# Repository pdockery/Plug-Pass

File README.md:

# Plug-Pass

Clatskanie People's Utility District (PUD) is a public, not-for-profit electric utility, governed by a locally-elected Board of Directors serving the Oregon communities and surrounding areas of Rainier, Westport, and Clatskanie.  The vast majority of our customers commute for work, and Clatskanie PUD designed its electric vehicle to minimize cost and maximize value for its commuting customers.  

Plug-Pass is a subscription-based, electric-vehicle public charging program developed to provide commuters easy access to low-cost charging service at their workplaces.  The first deployment of the Plug-Pass program was at a location where access to the parking spots was easily monitored, and the initial offering only used timers to control electricity.  In considering ways to expand the program to locations that aren't easily monitored, staff is developing low-cost control mechanisms to enable subscribers to initiate charging while preventing unauthorized parties from easily accessing the service.

This program is designed to be open-source in the hope that by sharing the program design broadly we may be able to expand the number of utilities employing similar techniques, and thereby lower the implementation costs for offering the program to more locations in our service territory.

Included in this repository is open-source information that has been used in our pilot program:
* Form of Electric Vehicle Public Charging Rate Design<br>
* Summary of Clatskanie PUD's Electric Vehicle Public Charging Program Design<br>
* Worksheet for calculating public charging rates (pending)<br>
* Form of Plug-Pass subscription agreement (pending)

Under development in this repository are open-source projects to be deployed and tested
* Software for arduino nano based plug-pass outlet control platform
* Control board design and configuration 
* Component list for Plug-Pass outlet

<b>For more information about Clatskanie PUD's EV charging program visit:<b>
https://clatskaniepud.com/ev

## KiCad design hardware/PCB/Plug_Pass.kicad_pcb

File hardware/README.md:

# Hardware

Contains the design files for the components for the switch including 
* KiCAD files for PCB
* FreeCAD files for 3D printable housing
* Bill of materials to assemble the switch

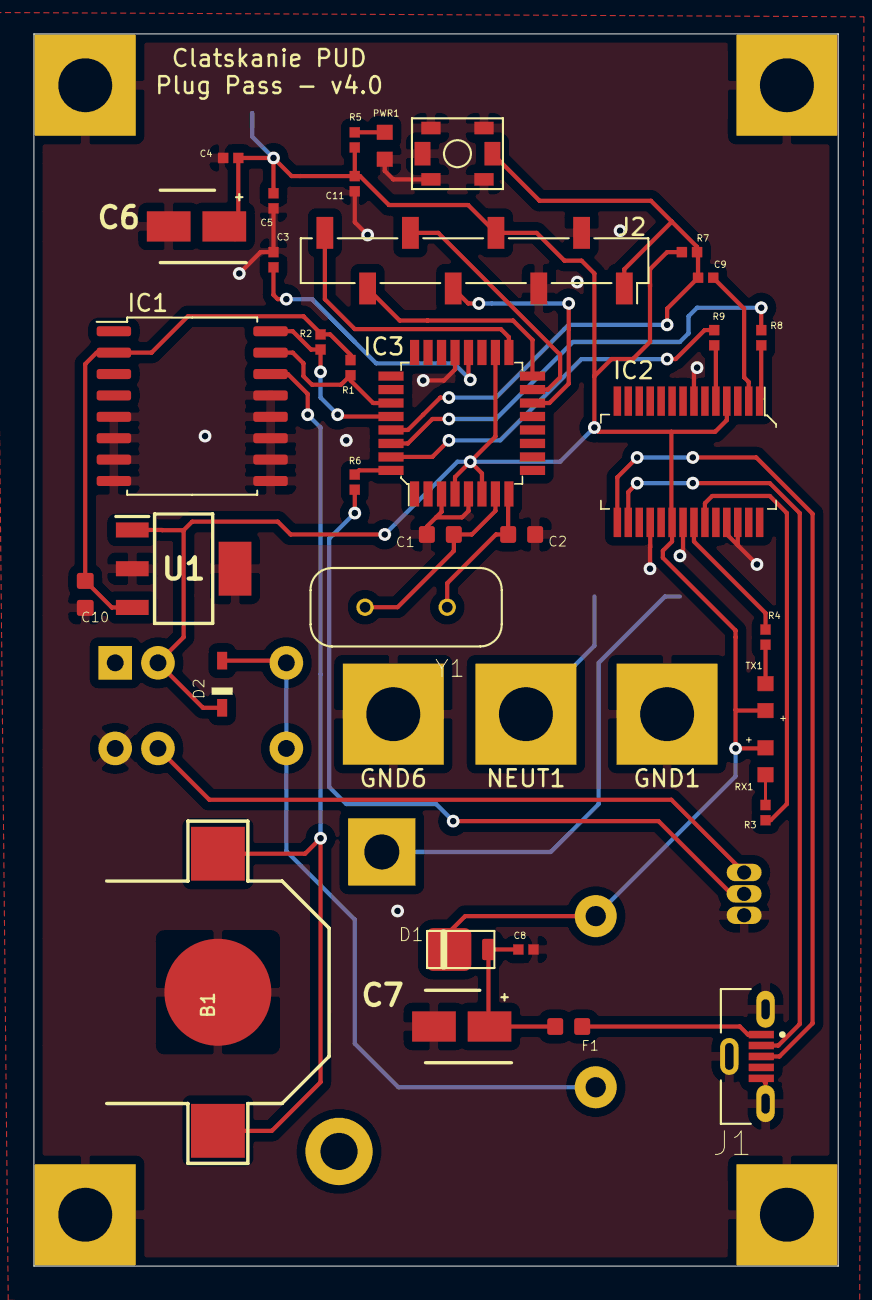
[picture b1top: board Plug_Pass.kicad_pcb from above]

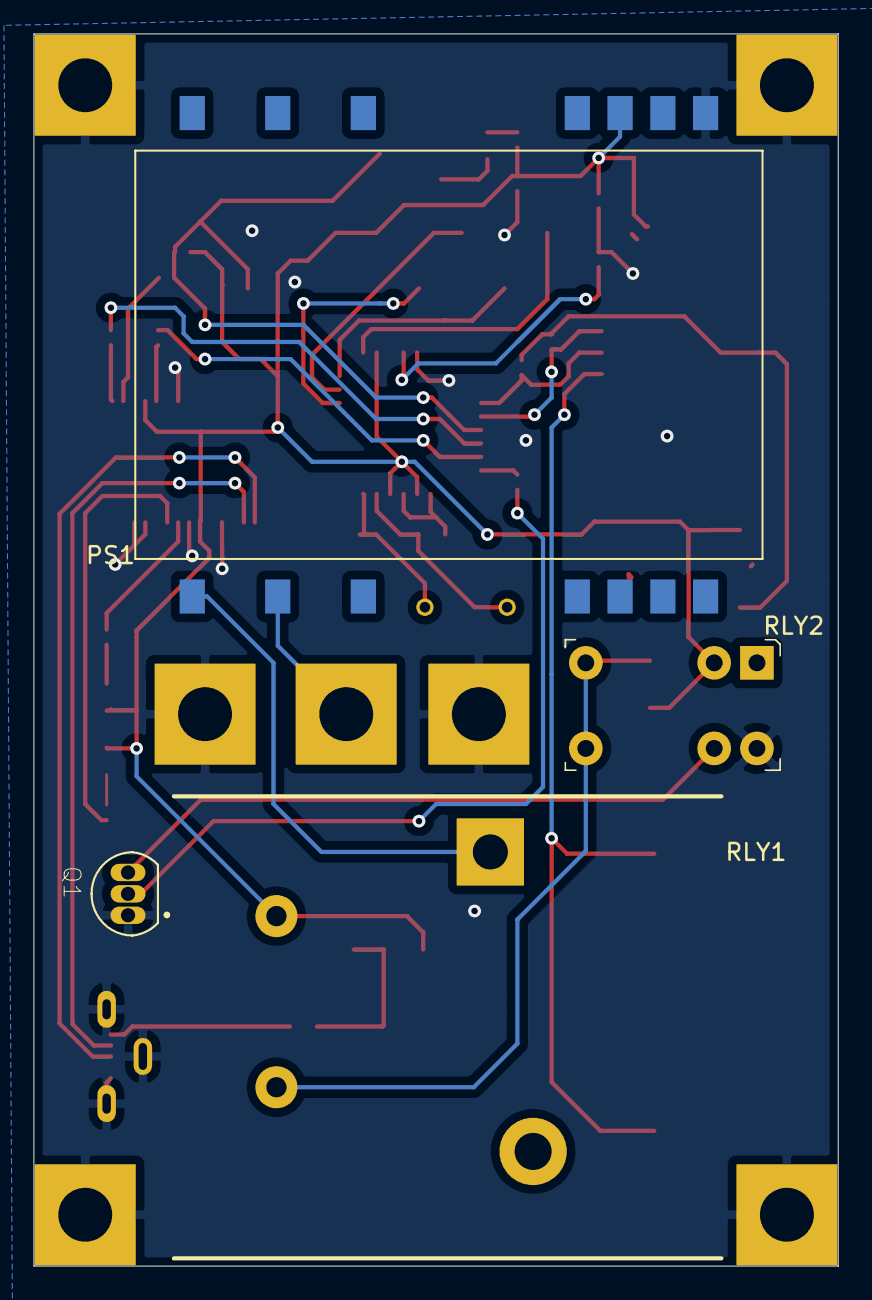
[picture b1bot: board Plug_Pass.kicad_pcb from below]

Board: 2 copper layers, 47.8 x 73.2 mm, 46 parts (4 on the bottom side), 34 nets.

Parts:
B1: CR1220
C1, C2: 22pF; 0603-1608X90N
C3, C8, C9: 100nF; 0402-1005X55N
C4, C5: 1µF; 0402-1005X55N
C6, C7: 4.7uF; CAPAE430X550N
C10: 1µF; 0603-1608X90N
C11: 1uF; 0402-1005X55N
D1: 0025_SS1P3L-M3_84A; DO220AAL
D2: 1N4148WS; SODFL2512X100N
F1: MFFSMF050; 0603-1608X90N
GND1, GND2, GND3, GND4, GND5, GND6: GND; Ground_Pad
IC1: DS3231M; SOIC-16W_7.5x10.3mm_P1.27mm
IC2: FT232RL; SSOP-28_W5.30mm
IC3: ATMEGA328P-AUR; TQFP-32_7x7mm
J1: USB_B_Micro; MOLEX_1051330001
J2: Conn_01x08; PinSocket_1x08_P2.54mm_Vertical_SMD_Pin1Right
NEUT1: NEUT; Ground_Pad
PS1: IRM-03-5; Converter_ACDC_MeanWell_IRM-03-xx_SMD
PWR1: Green; LEDC1608X80N-AK
Q1: 2N3904; TO92127P495H495-3
R1, R2: 10k; 0402-1005X55N
R3, R4, R5: 330; 0402-1005X55N
R6: 4.7k; 0402-1005X55N
R7, R8, R9: 1k; 0402-1005X55N
RLY1: T95S5D22-5; RLY-T9AS1D22-5
RLY2: G5V-1-DC5; Relay_THT_G5V-1
RX1: Red; LEDC1608X80N-AK
SW1: RESET; C&K_PTS820_NO_HOLES
TX1: Green; LEDC1608X80N-AK
U1: TC1108-3.3VDBTR; SOT230P700X180-4N
Y1: ECS-51-20-4; XTAL_ECS-51-20-4

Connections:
+3V3: C10.1, IC1.2, R1.2, R2.2, U1.3
+5V: C4.1, C5.1, C6.1, C11.1, D1.P$1, D2.C, IC2.4, IC2.20, IC3.4, IC3.6, IC3.18, J2.4, PS1.16, R5.1, R7.2, RLY1.5, RLY2.2, RX1.A, TX1.A, U1.1
/BAT+: B1.+$1, IC1.14
/D+: IC2.15, J1.3
/D-: IC2.16, J1.2
/NEUT: NEUT1.1, PS1.3
/RX_RED: IC2.23, R3.1
/TX_GREEN: IC2.22, R4.1
AC-L: PS1.1, RLY1.1
GNDREF: B1.-, C1.1, C2.1, C3.2, C4.2, C5.2, C6.2, C7.2, C8.2, C10.2, C11.2, GND1.1, GND2.1, GND3.1, GND4.1, GND5.1, GND6.1, IC1.5, IC1.6, IC1.7, IC1.8, IC1.9, IC1.10, IC1.11, IC1.12, IC1.13, IC2.7, IC2.18, IC2.21, IC2.25, IC2.26, IC3.3, IC3.5, IC3.21, J1.5, J1.S, J2.2, J2.3, PS1.14, PWR1.C, Q1.1, RLY2.10, SW1.1, SW1.3, SW1.4, SW1.5, SW1.6, U1.2, U1.4
MISO: IC3.16, J2.7
MOSI: IC3.15, J2.6
unnamed: C1.2, IC3.7, Y1.2
unnamed: C2.2, IC3.8, Y1.1
unnamed: C3.1, IC3.20
unnamed: C7.1, C8.1, D1.P$2, F1.2
unnamed: C9.2, IC2.2
unnamed: D2.A, RLY1.2, RLY2.5, RLY2.6
unnamed: F1.1, J1.1
unnamed: IC3.30, R8.1
unnamed: IC3.31, R9.1
unnamed: PWR1.A, R5.2
unnamed: Q1.2, R6.1
unnamed: Q1.3, RLY2.9
unnamed: R3.2, RX1.C
unnamed: R4.2, TX1.C
RESET: C9.1, IC3.29, J2.1, R7.1, SW1.2
RLY: IC3.32, R6.2
RX: IC2.1, R8.2
SCK: IC3.17, J2.8
SCL: IC1.16, IC3.28, R2.1
SDA: IC1.15, IC3.27, R1.1
SS: IC3.14, J2.5
TX: IC2.5, R9.2

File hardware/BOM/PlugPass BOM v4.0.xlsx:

Item # | Quantity | Reference | Value | Footprint | Description | MPN | Manufacturer | Type | Link
1.0 | 2.0 | C1, C2 | 22pF | 0603-1608X90N | Multilayer Ceramic Capacitors MLCC - SMD/SMT 22pF 50V NPO 5% | CC0603JRNPO9BN220 | Yageo | SMD | https://www.mouser.com/ProductDetail/Yageo/CC0603JRNPO9BN220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
2.0 | 3.0 | C3, C8, C9 | 100nF | 0402-1005X55N | Multilayer Ceramic Capacitors MLCC - SMD/SMT .1UF 50V 5% 0402 | GRM155R61H104JE14D | Murata Electronics | SMD
3.0 | 2.0 | C4, C5 | 1µF | 0402-1005X55N | Multilayer Ceramic Capacitors MLCC - SMD/SMT 0402 25VDC 1uF 10% | GRM155R61E105KA12D | Murata Electronics | SMD
4.0 | 2.0 | C6, C7 | 4.7µF | CAPAE430X550N | Aluminum Electrolytic Capacitors - SMD WCAP-ASNP 4.7uF 16V 20% SMD/SMT | 865250340002 | Wurth Elektronik | SMD
7.0 | 2.0 | C10, C11 | 1uF | 0402-1005X55N | Multilayer Ceramic Capacitors MLCC - SMD/SMT 0402 25VDC 1uF 10% | GRM155R61E105KA12D | Murata Electronics | SMD
8.0 | 2.0 | R1, R2 | 10k | 0402-1005X55N | Thick Film Resistors - SMD 10K OHM 1% | RC0402FR-0710KL | Yageo | SMD
9.0 | 3.0 | R3, R4, R5 | 330.0 | 0402-1005X55N | Thick Film Resistors - SMD 330 OHM 1% | RC0402FR-07330RL | Yageo | SMD
10.0 | 1.0 | R6 | 4.7k | 0402-1005X55N | Thick Film Resistors - SMD 4.7 kOhms 62.5 mW 0402 5% | RC0402JR-7D4K7L | Yageo | SMD | https://www.mouser.com/ProductDetail/Yageo/RC0402JR-7D4K7L?q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
11.0 | 3.0 | R7, R8, R9 | 1k | 0402-1005X55N | Thick Film Resistors - SMD 1 kOhms 62.5 mW 0402 5% | RC0402JR-071KL | Yageo | SMD
12.0 | 1.0 | IC1 | DS3231M | Package_SO:SOIC-16W_7.5x10.3mm_P1.27mm | Real Time Clock +/-5ppm, I C Real-Time Clock | DS3231M+ | Maxim Integrated | SMD
13.0 | 1.0 | IC2 | FT232RL | digikey-footprints:SSOP-28_W5.30mm | IC USB FS SERIAL UART 28-SSOP |  | FTDI, Future Technology Devices International Ltd | SMD
14.0 | 1.0 | IC3 | ATMEGA328P-AUR | digikey-footprints:TQFP-32_7x7mm | IC MCU 8BIT 32KB FLASH 32TQFP | ATMEGA328P-AUR | Microchip Technology | SMD
15.0 | 1.0 | SW1 | RESET | C&K_PTS820_NO_HOLES | Tactile Switches Microminiature SMT Top Actuated | PTS820J25KSMTRLFS | C&K | SMD
16.0 | 1.0 | RX1 | Red | LEDC1608X80N-AK | Standard LEDs - SMD Red Diffused 639nm 17mcd | HSMH-C190 | Broadcom | SMD
17.0 | 1.0 | TX1 | Green | LEDC1608X80N-AK | Standard LEDs - SMD Green Diffused 572nm 5mcd | HSMG-C190 | Broadcom | SMD
18.0 | 1.0 | PWR1 | Green | LEDC1608X80N-AK | Standard LEDs - SMD Green Diffused 572nm 5mcd | HSMG-C190 | Broadcom | SMD
19.0 | 1.0 | D1 | 0025_SS1P3L-M3_84A | DO220AAL | Schottky Diodes & Rectifiers 30volt 1.0amp | SS1P3L-M3/84A | Vishay Semiconductors | SMD
20.0 | 1.0 | D2 | NA | SODFL2512X100N | DIODE GEN PURP 75V 150MA SOD323F | 1N4148WS | ON Semiconductor | SMD | https://www.digikey.com/en/products/detail/on-semiconductor/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
21.0 | 1.0 | RLY1 | T9AS1D22-5 | RLY-T9AS1D22-5 | RELAY GEN PURPOSE SPST 30A 5V | T9AS1D22-5 | TE Connectivity Potter & Brumfield Relays | through-hole
22.0 | 1.0 | RLY2 | G5V-1-DC5 | Relay_THT_G5V-1 | RELAY GEN PURPOSE SPDT 1A 5VDC | G5V-1-DC5 | Omron Electronics Inc-EMC Div | through-hole
23.0 | 1.0 | B1 | CR1220 | CR1220 | CR1220 COIN CELL SM RETAINER | 2894 | Keystone Electronics | SMD
24.0 | 1.0 | Y2 | 16Mhz | HU-49USX | 16Mhz Crystal | ECS-160-18-4X-CKM | ECS | through-hole
25.0 | 1.0 | J1 | USB_B_Micro | MOLEX_1051330001 | USB Connectors MICRO USB B RECPT VERTICAL | 1051330001 | Molex | SMD & through-hole
26.0 | 1.0 | J2 | 1x8 | PinSocket_1x08_P2.54mm_Vertical_SMD_Pin1Right | CONN HDR 8POS 0.1 TIN SMD | NPTC081KFXC-RC | NA | SMD | https://www.digikey.com/en/products/detail/sullins-connector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
27.0 | 1.0 | Q1 | NA | TO-92-3 | BJT | 2n3904 | OnSemi | through-hole | https://www.mouser.com/Semiconductors/Discrete-Semiconductor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
28.0 | 1.0 | F1 | MFFSMF050 | 0603-1608X90N | Resettable Fuses - PPTC 6volts 40amps | MF-FSMF050X-2 | Bourns | SMD
29.0 | 1.0 | U1 | 3.3v | SOT-223-3 | 3.3v Regulator | TC1108-3.3VDBTR | Microchip | SMD | https://www.mouser.com/ProductDetail/579-TC1108-3.3VDBTR
30.0 | 1.0 | PS1 | IRM-03-5 | Converter_ACDC:Converter_ACDC_MeanWell_IRM-03-xx_SMD | AC/DC CONVERTER 5V 3W | IRM-03-5S | MEAN WELL USA Inc. | SMD

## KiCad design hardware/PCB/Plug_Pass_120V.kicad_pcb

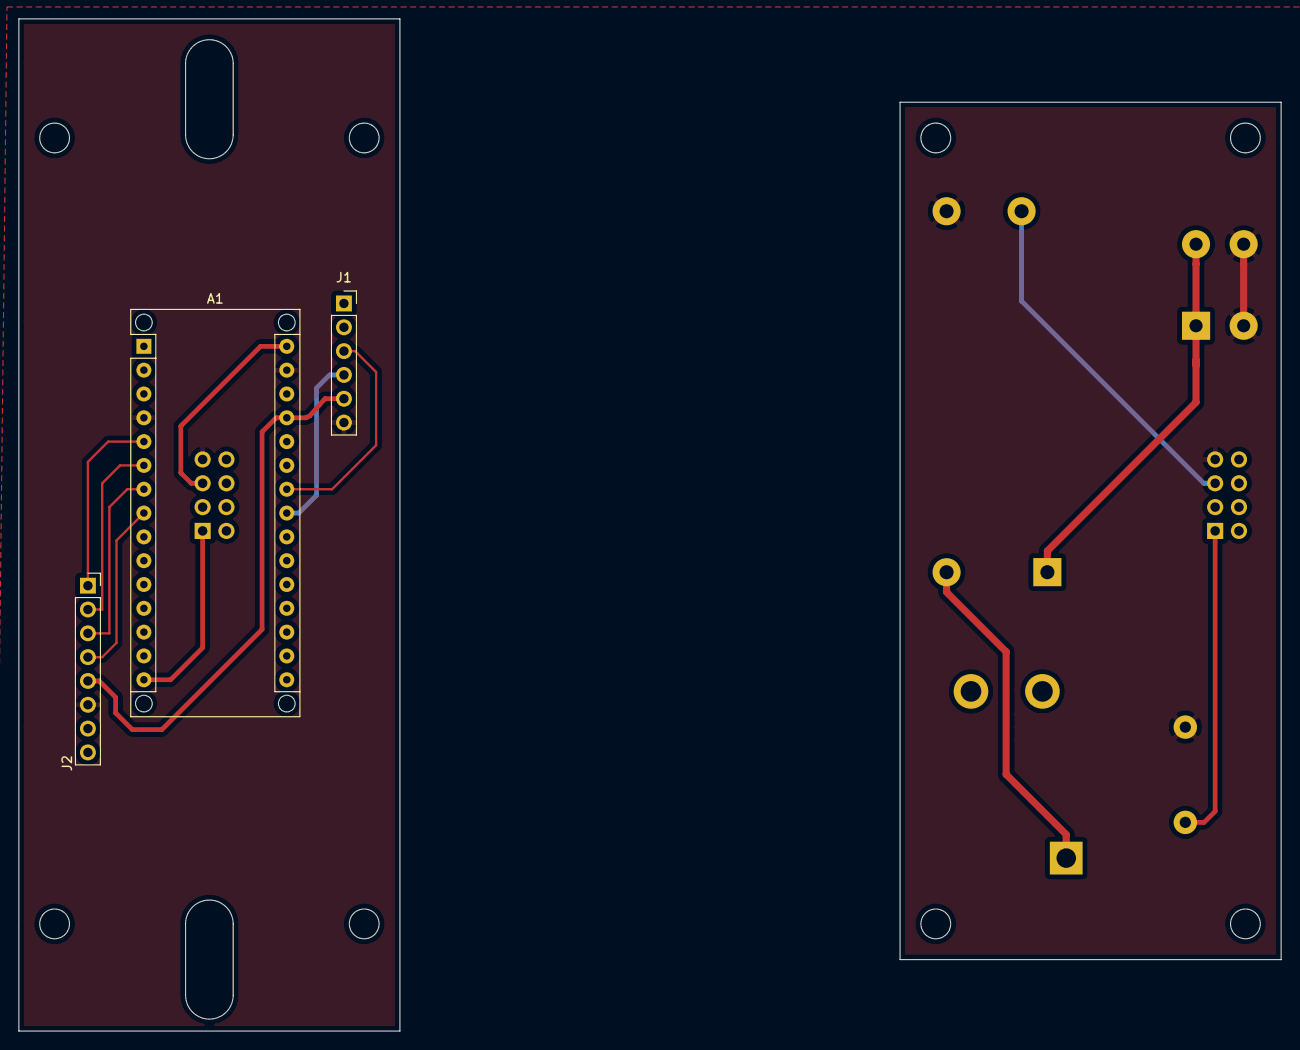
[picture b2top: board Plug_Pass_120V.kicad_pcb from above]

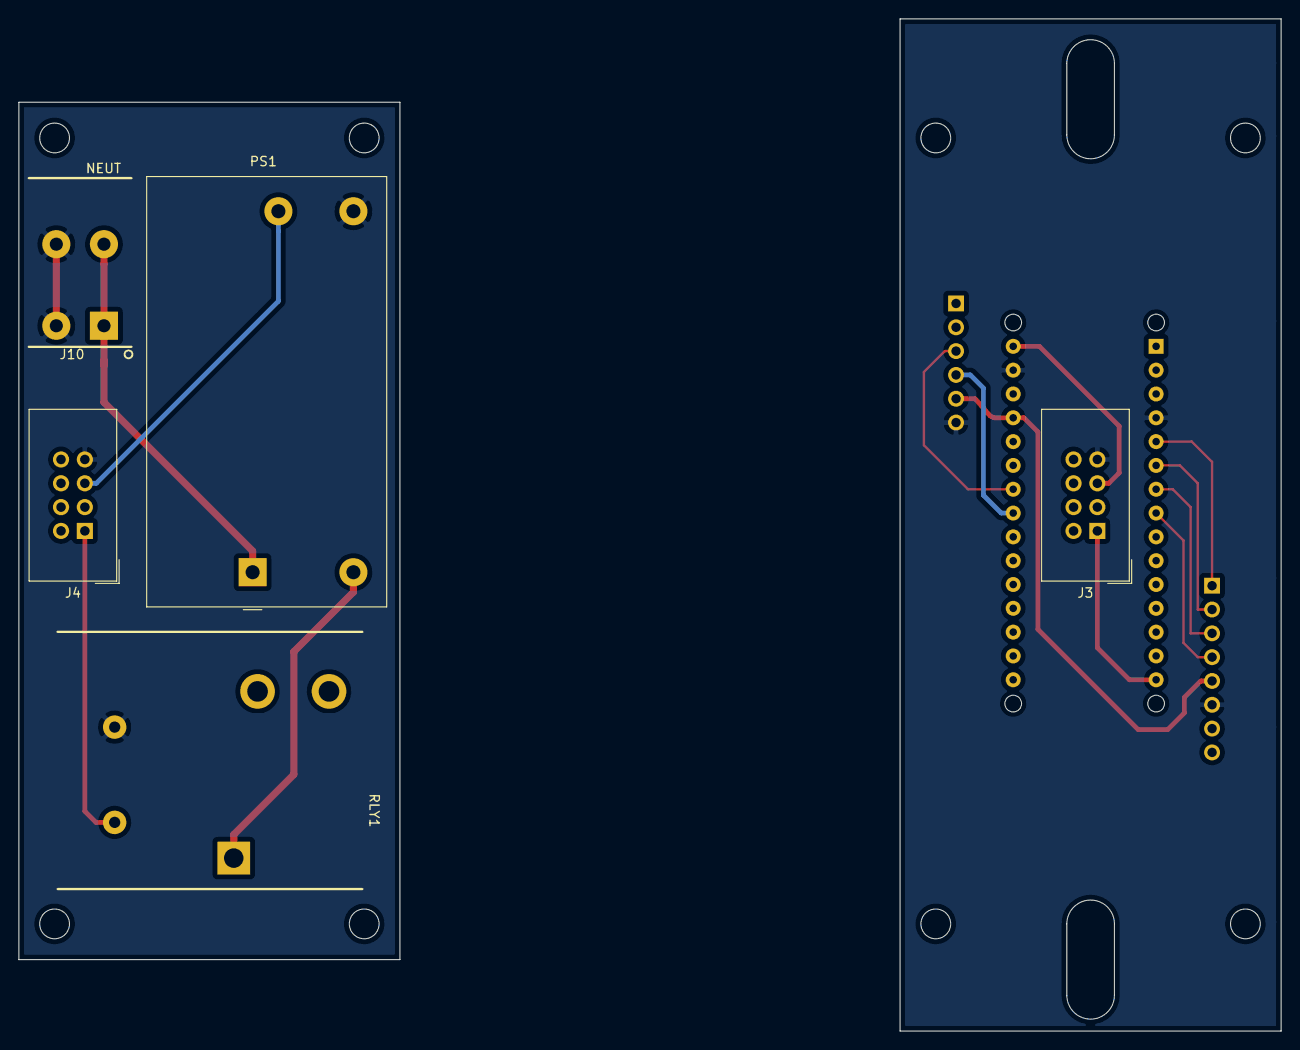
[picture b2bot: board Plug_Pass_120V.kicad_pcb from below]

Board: 2 copper layers, 134.6 x 108.0 mm, 8 parts (5 on the bottom side), 12 nets.

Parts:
A1: Arduino_Nano_v3.x; Arduino_Nano_WithMountingHoles
J1: Conn_01x06; PinSocket_1x06_P2.54mm_Vertical
J2: Conn_01x08; PinSocket_1x08_P2.54mm_Vertical
J3, J4: Conn_02x04_Odd_Even; IDC-Header_2x04_P2.54mm_Vertical
J10: TDPT-1017503; TDPT_2P_5.08MM
PS1: IRM-05-5; Converter_ACDC_MeanWell_IRM-05-xx_THT
RLY1: T95S5D22-5; RLY-T9AS5D22-5

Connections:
+5V: A1.27, J1.5, J2.5
/MISO: A1.6, J2.2
/MOSI: A1.7, J2.3
/RelayPin: A1.15, J3.1, J4.1, RLY1.5
/SCK: A1.5, J2.1
/SCL: A1.24, J1.3
/SDA: A1.23, J1.4
/SS: A1.8, J2.4
GNDREF: A1.4, A1.29, J1.6, J2.6, J3.7, J4.7, J10.2, PS1.3, RLY1.2
unnamed: PS1.2, RLY1.1
unnamed: J10.1, PS1.1
VCC: A1.30, J3.5, J4.5, PS1.4

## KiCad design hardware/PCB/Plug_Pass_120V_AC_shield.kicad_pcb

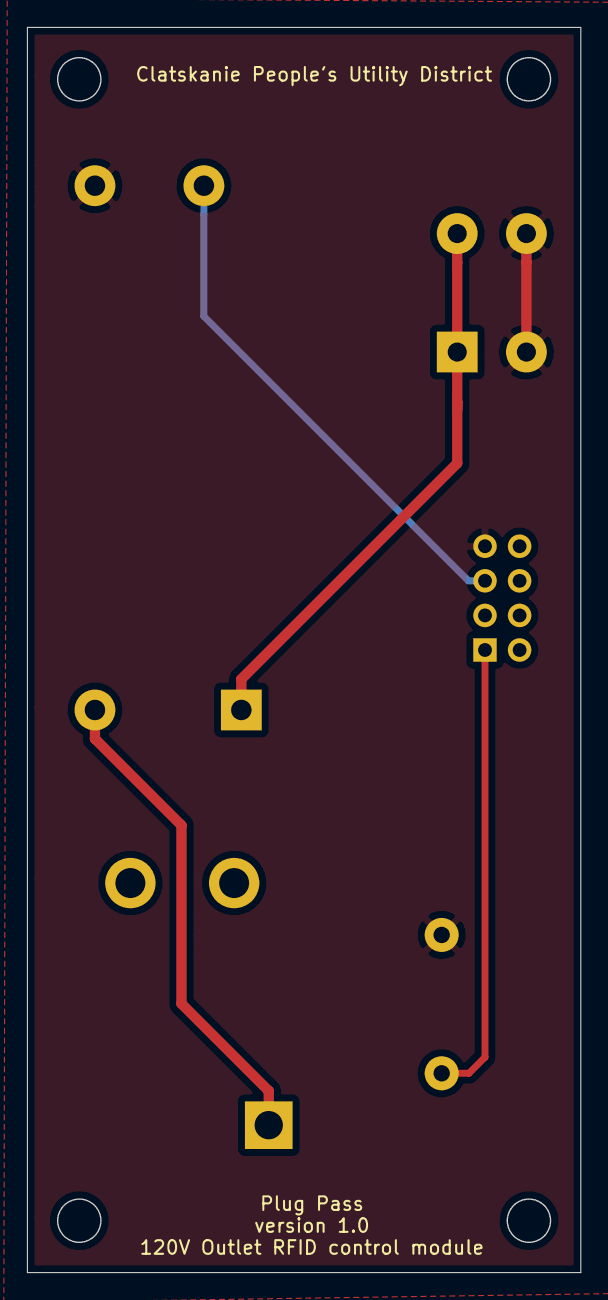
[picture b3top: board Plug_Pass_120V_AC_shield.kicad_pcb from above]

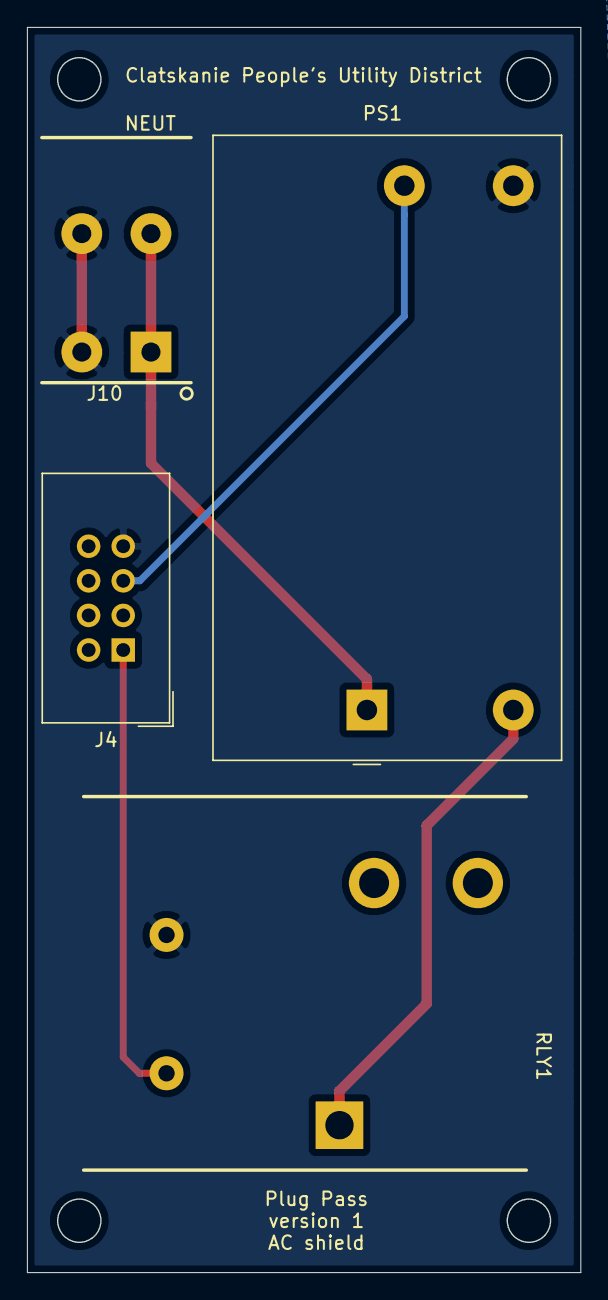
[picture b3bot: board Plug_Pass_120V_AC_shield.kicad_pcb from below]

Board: 2 copper layers, 40.6 x 91.4 mm, 4 parts (4 on the bottom side), 5 nets.

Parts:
J4: Conn_02x04_Odd_Even; IDC-Header_2x04_P2.54mm_Vertical
J10: TDPT-1017503; TDPT_2P_5.08MM
PS1: IRM-05-5; Converter_ACDC_MeanWell_IRM-05-xx_THT
RLY1: T95S5D22-5; RLY-T9AS5D22-5

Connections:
/RelayPin: J4.1, RLY1.5
GNDREF: J4.7, J10.2, PS1.3, RLY1.2
unnamed: PS1.2, RLY1.1
unnamed: J10.1, PS1.1
VCC: J4.5, PS1.4

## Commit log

2020-02-26 Create Arduino_Sketch_file
2020-02-26 Add arduino sketch
2020-03-03 syntax error corrected
    found a syntax error in RfidDb reference. The changed code compiles and reads a card.
2020-03-04 commented out while loop
    there was a while look that kept looping and locked up the code. commented out. also added some time prints to check if it went through the loop.
2020-03-04 Update plug_pass_prototype_0_1.ino
    I added some comments explaining the includes as well as confirming the RfidDb constructor parameters as explained in the RfidDb.h file.
    We could also include a file with accepted rfid keys and compare against it rather than using RfidDb.
    I think RfidDb would only be necessary if we were adding more keys at runtime rather than during a full firmware update.
2020-03-05 Update to print legible dates to serial monitor
    Updated date formats so it prints something legible to the serial monitor. (mostly a learning experiment)
2020-03-06 Now enables relay on digital pin 12
    Also moved the date printing to a single function to clean the code up a bit. For testing purposes the relay is triggered for 3 seconds on startup if there is still time remaining on the last charge 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
2020-03-07 Update to timeout the card read function
    this will loop, wait for a card read for 5 seconds, then loop again.
2020-03-09 Update from Sunday fiddling
    this is the code we fiddled around with Sunday.
2020-03-09 First stage - this is not done
    not done, but cleaned alittle. have been working on the time issue. i think it's either a bad module or a bad battery.
2020-03-09 Update mister-clean
    I'm pretty happy with the clean up. I also added a functionality that allows us to turn off the outlet by nfc scan. I took out all the db stuff.
2020-03-11 Update added a watcher on the walls
    Added a validation step to compare the UID of the card that was scanned against a known UID. Packaged the reading of the UID as a sub-function so it doesn't clutter up the main code. What do you thin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
2020-03-11 Simple update - delay on wrong card
    Added a short delay on scanning a card with the wrong code.
2020-03-12 Update - variable data types
    Updated variable data types for the timeout in the card reader, and the charge time.
2020-03-12 data type data type data type
    i keep messing up data types. aligned data types for the charge_time and chargeStart variables so they calculate faster.
2020-03-16 Update - defines a chargeStatus variable
    created a chargeStatus variable to hold the most recent command of off or on that i can reference instead of reading the pin status.
2020-03-16 Update - clean up variables
    changed formatting of some variables to make them consistent.
2020-04-02 Upload Example EV Public Charging Rate Schedule
2020-04-02 Rename plug_pass_prototype_0_1.ino to plug_pass_control_protocol.ino
2020-04-02 Update with website
2020-04-07 Added Example Rate Schedule to subfolder
2020-04-07 Move plug_pass_control_protocol into subfolder
    Move plug_pass_control_protocol into firmware subfolder in order to force some organization to the page
2020-04-07 Create gitignore for subfolder
2020-04-07 create PCB subfolder in hardware
2020-04-07 add KiCAD files
2020-04-07 Create README.md in hardware
2020-04-07 Create README.md for documentation
2020-04-07 Create README.md in firmware
2020-04-07 put gitignore in root
2020-04-08 Upload KiCAD files
2020-04-08 create gitignore file in pcb directory
2020-04-10 add current files through upload
    includes revised schematic and updated library with parts
2020-04-13 Update plug_pass_control_protocol.ino
    reconfigured the SPI wiring so that the wires didn't have to cross. thought it might make wiring and pcb printing a little easier.
2020-04-13 Schematic update for SPI wiring of NFC reader
    Corresponding update to the PCB schematic to correspond to the firmware update.
2020-04-15 Uploaded revised schematic and pcb layout
    Uploaded revisions to the KiCAD schematic, and included phase 1 of the PCB layout design process.
2020-04-16 Version 1 of a full PCB design
    This push has a full KiCAD package for a set of boards. Still in draft, but it's complete.
2020-04-16 Create LayoutLibrary
2020-04-16 Added footprints folder
2020-04-21 Revised KiCAD project
    added a 120V schematic and pcb board layout that reduces the footprint so it fits in a normal 120V switch slot.
2020-04-21 upload most recent KiCAD files
    Revised KiCAD footprint files in most recent iteration.
2020-04-22 KiCAD files from first prototype batch
2020-04-22 KiCAD gerber files from first prototype board
2020-05-14 Add initialization file
    sets up both the arduino and the rfid cards
2020-05-28 add revised pcb parts list
2020-06-30 Version 2.0 of the 3D printed enclosure
2020-08-24 Update plug_pass_control_protocol.ino
    found a better way to set the charge ending time
2020-12-08 Create BOM
2021-05-20 Added platformio project, moved arduino sketches to their own folder
2021-05-20 Changed build to correct board
2021-05-20 Changed project default baud rate to 115200
2021-05-20 Added relay class
2021-05-21 Code used to validate board modules
2021-06-09 Test code cleanup
2021-06-09 Board update v3.2
2021-12-14 Update 4
2021-12-16 Toggle outlet on swipe
2021-12-16 Push additional changes for toggle outlet
2021-12-16 Fix toggle issue
2021-12-16 More stuff
2021-12-16 longer delay - rescans
